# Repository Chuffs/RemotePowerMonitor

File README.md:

# Remote Power Outage Detection & Alert System
This Github repository and project outlines the usage of an Arduino Based ESP8266 WiFi and Bluetooth Module along with a WaveShare SIM7000E NB-IoT / Cat-M / EDGE / GPRS Module in creating an alert system for a remote site power outage.

---

## Versions
- [V0.1a](#v01a)
- [V0.2a](#v02a) - Current Version
---

## Background
During the summer in outback Queensland, temperatures can exceed 50°C. ALong with the high temperatures weather can be rather sporadic, with sudden flash flooding and lightning storms. This can cause havoc with the electricity network with unplanned outages. A lot of properties in outback Queensland are far from any town and getting notified of a power outage is incredibly rare. In order to avoid rotten food in both fridges and freezers I wanted to create a device that could notify me of a power outage so that I could take appropriate action to save, or at least salvage, food and perishables at these remote locations.

## Initial Drawing of Idea
Simply put we needed a system that could detect the power outage which then alerted some form of microcontroller to then send an alert to myself to notify/warn of the power outage. In order to actually do this, in the case of a power outage, this system would need to be battery operated so that it could continue after power was removed from the site.

# V0.1a
This version used the below components to detect and alert of a power outage.

- [WaveShare SIM7000E][def]
    - *Only LTE Capable module available in Australia at time of purchase*
- [ESP8266 WiFi Board - XC3082][def2]
    - *Small Footprint, Cheap cost and easy to access. Uses the Arduino library and IDE for ease of programming and debugging*
- [XC4502][def4] paired with an [XC4512][def5], a cheap and small footprint LiPo charger and 5v boost module.
- 10k - 10k voltage divider with a 5v Wall Plug into the analog pin of the ESP8266
- Telstra Cat-M SIM Card

## What went well?
- Proof of concept for sending an SMS on an external trigger (analog pin falling below a certain threshold)
- Footprint of prototype, could all be contained within a small jiffy type container.

## ~~Bugs~~ "Features" and what had to be improved on:
- Source of heat in the winter - The XC4502 and the XC4512 cannot be used simultaneously. Loading the battery caused the charger module to think that the battery needed charging and therefore pumped in more voltage causing parts to overheat.
- The usage of the 10k - 10k voltage divider was to ensure that the voltage going into the analog pin didn't exceed the maximum voltage. However, connecting the external 5v and the 5v boost module's ground together caused some strange behavior on the analog to digital conversion in code.
- The price of maintaining a cellular capable SIM was extortionate when considering the usage of this device would probably be a couple times a month during summer or rather 4-6 months of the year.

# V0.2a
This version included a multitude of updates making the system more reliable and user friendly, including a WebUI for configuring and customizing the alerts to be sent. The detection system also had an overhaul and the charging functionality was completely removed.

The code was changed to incorporate the deep sleep functionality of the ESP Family.

One additional part was added in this version - [LiteOn 4N25 Optocoupler][def7]. This allowed the 5v Wall Adapter to be completely separated and isolated from the ESP and Modem.

With testing complete a pcb prototype of this version was made - KiCAD Project Files can be found under this [folder][def8].

## What went well

## What needs improved on

Psuedo code or flow chart was as follows.

[def]: https://www.waveshare.com/sim7000e-nb-iot-hat.htm
[def2]: https://www.jaycar.com.au/wifi-mini-esp8266-main-board/p/XC3802
[def3]: https://www.kynix.com/editor_u/pdf/20220117/IP5306.pdf
[def4]: https://www.jaycar.com.au/arduino-compatible-lithium-battery-usb-charger-module/p/XC4502
[def5]: https://www.jaycar.com.au/arduino-compatible-5v-dc-to-dc-converter-module/p/XC4512
[def6]: https://www.dfrobot.com/product-1613.html
[def7]: https://au.mouser.com/datasheet/2/239/775704_1-1175530.pdf
[def8]: https://github.com/Chuffs/RemotePowerMonitor/tree/main/v0.2a/v0.2a

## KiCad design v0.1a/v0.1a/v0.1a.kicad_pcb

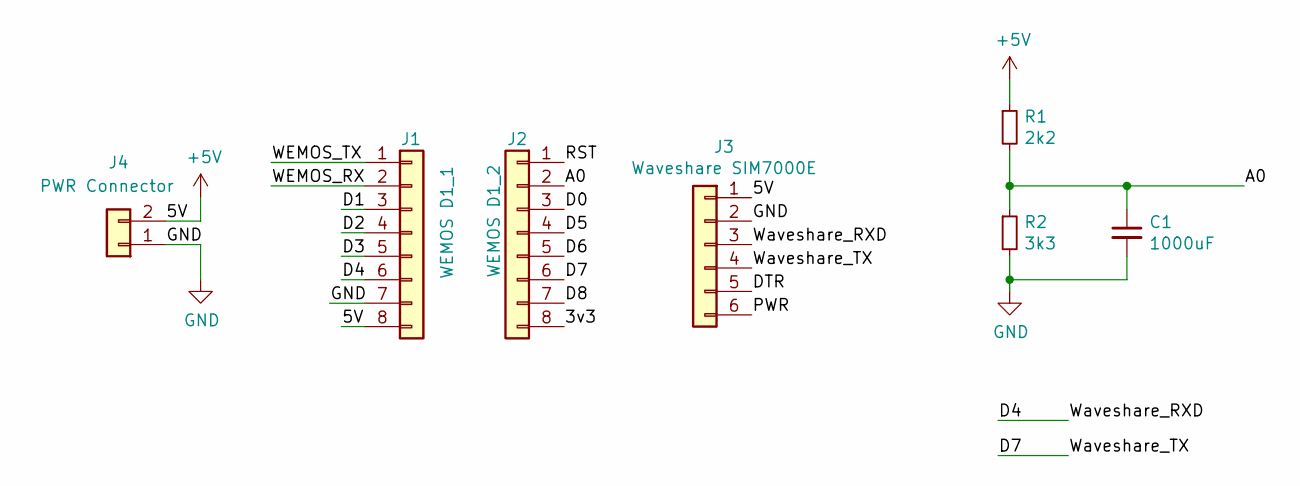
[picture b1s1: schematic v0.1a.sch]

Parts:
C1: 1000uF; CP_Radial_D10.0mm_P2.50mm_P5.00mm
J1: WEMOS D1_1; PinHeader_1x08_P2.54mm_Vertical
J2: WEMOS D1_2; PinHeader_1x08_P2.54mm_Vertical
J3: Waveshare SIM7000E; PinHeader_1x06_P2.54mm_Vertical
J4: PWR Connector; PinHeader_1x02_P2.54mm_Vertical
R1: 2k2; R_Axial_DIN0411_L9.9mm_D3.6mm_P25.40mm_Horizontal
R2: 3k3; R_Axial_DIN0411_L9.9mm_D3.6mm_P25.40mm_Horizontal

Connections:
+5V: J1.8, J3.1, J4.2, R1.1
/3v3: J2.8
/A0: C1.1, J2.2, R1.2, R2.1
/D0: J2.3
/D1: J1.3
/D2: J1.4
/D3: J1.5
/D4: J1.6, J3.3
/D5: J2.4
/D6: J2.5
/D7: J2.6, J3.4
/D8: J2.7
/DTR: J3.5
/PWR: J3.6
/RST: J2.1
/WEMOS_RX: J1.2
/WEMOS_TX: J1.1
GND: C1.2, J1.7, J3.2, J4.1, R2.2

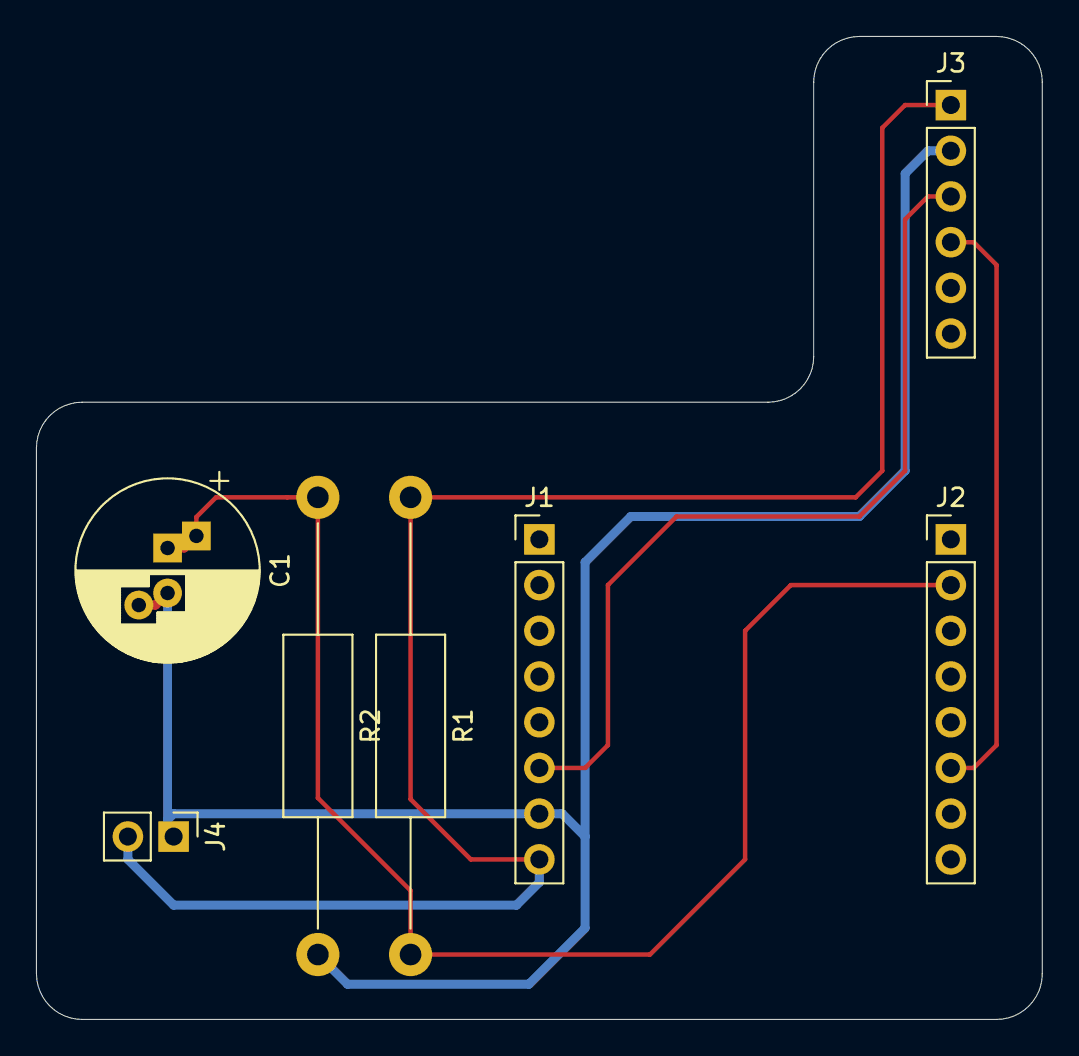
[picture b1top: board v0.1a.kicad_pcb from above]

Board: 2 copper layers, 55.9 x 54.6 mm, 7 parts (0 on the bottom side), 5 nets.

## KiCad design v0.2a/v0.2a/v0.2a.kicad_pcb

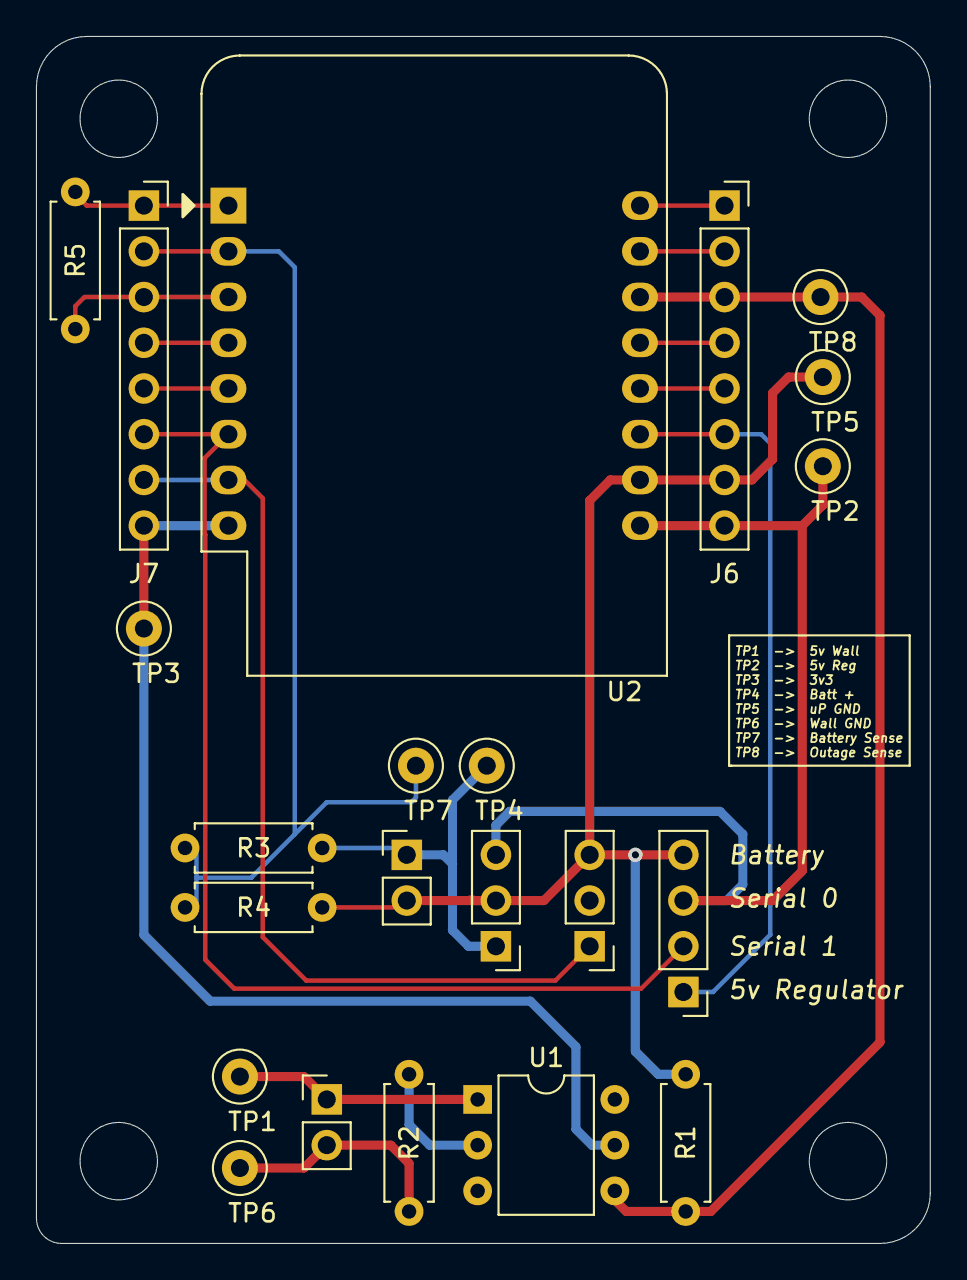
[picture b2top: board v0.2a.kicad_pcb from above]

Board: 2 copper layers, 49.7 x 67.1 mm, 22 parts (0 on the bottom side), 20 nets.

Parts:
J1: Battery; PinHeader_1x02_P2.54mm_Vertical
J2: 5v Regulator; PinHeader_1x03_P2.54mm_Vertical
J3: 5v Wall; PinHeader_1x02_P2.54mm_Vertical
J4: Serial 0; PinHeader_1x03_P2.54mm_Vertical
J5: Serial 1; PinHeader_1x04_P2.54mm_Vertical
J6: Wemos RHS; PinSocket_1x08_P2.54mm_Vertical
J7: Wemos LHS; PinSocket_1x08_P2.54mm_Vertical
R1, R3, R4: 10k; R_Axial_DIN0207_L6.3mm_D2.5mm_P7.62mm_Horizontal
R2: 50; R_Axial_DIN0207_L6.3mm_D2.5mm_P7.62mm_Horizontal
R5: 470; R_Axial_DIN0207_L6.3mm_D2.5mm_P7.62mm_Horizontal
TP1: 5v Wall; TestPoint_Loop_D2.50mm_Drill1.0mm_LowProfile
TP2: 5v Regulator; TestPoint_Loop_D2.50mm_Drill1.0mm_LowProfile
TP3: 3v3 Regulator; TestPoint_Loop_D2.50mm_Drill1.0mm_LowProfile
TP4: Battery +; TestPoint_Loop_D2.50mm_Drill1.0mm_LowProfile
TP5: uP GND; TestPoint_Loop_D2.50mm_Drill1.0mm_LowProfile
TP6: Wall GND; TestPoint_Loop_D2.50mm_Drill1.0mm_LowProfile
TP7: Battery_Sense; TestPoint_Loop_D2.50mm_Drill1.0mm_LowProfile
TP8: Outage_Sense; TestPoint_Loop_D2.50mm_Drill1.0mm_LowProfile
U1: 4N25; DIP-6_W7.62mm
U2: WeMos_D1_mini; WEMOS_D1_mini_light

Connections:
+3V3: J7.8, TP3.1, U1.5, U2.8
+5V: J3.1, TP1.1, U1.1
+5VA: J2.3, J5.3, J6.8, TP2.1, U2.9
/A0: J7.2, R3.2, R4.1, TP7.1, U2.2
/Batt+: J1.1, J2.1, R3.1, TP4.1
/Batt-: J1.2, J2.2, J4.3, J5.4, J6.7, R1.2, R4.2, TP5.1, U2.10
/D0: J7.3, R5.1, U2.3
/D1: J6.3, R1.1, TP8.1, U1.4, U2.14
/D2: J6.4, U2.13
/D3: J6.5, U2.12
/D4: J5.1, J6.6, U2.11
/D5: J7.4, U2.4
/D6: J7.5, U2.5
/D7: J5.2, J7.6, U2.6
/D8: J4.1, J7.7, U2.7
/GND_wall: J3.2, R2.2, TP6.1
/RST: J7.1, R5.2, U2.1
/Rx: J6.2, U2.15
/Tx: J6.1, U2.16
unnamed: R2.1, U1.2

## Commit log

2022-05-03 init_comit
2022-06-24 v0.2a
2022-10-02 Gerber File Creation
2022-10-02 Folder Cleanup
    Created GitIgnore
2022-10-03 gitignore update
2022-10-13 README
    Created readme file
2022-10-13 Stashed v0.1a
2022-10-22 KiCad Update
    Updated files to v6 KiCad
